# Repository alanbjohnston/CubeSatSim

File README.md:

# CubeSatSim

The CubeSat Simulator https://github.com/alanbjohnston/CubeSatSim/wiki is a low cost satellite emulator that runs on solar panels and batteries, transmits UHF radio telemetry, has a 3D printed frame, and can be extended by additional sensors and modules.  This project is sponsored by the not-for-profit [Radio Amateur Satellite Corporation, AMSAT®](https://amsat.org) https://CubeSatSim.org

The three custom PCBs are the Main, Battery and Solar boards.  Information including schematics and gerbers is in https://CubeSatSim.org/hardware

For information about the AMSAT STEM education program based on the CubeSatSim, see https://CubeSatSim.org/EducatorsGuide

For STEM activities to do with the CubeSatSim, see the https://CubeSatSim.org/ActivityGuides

There are several hardware versions and software branches to go with them - see below for information.

See the Wiki Software Install page for more details: https://github.com/alanbjohnston/CubeSatSim/wiki/2.-Software-Install. The software runs the Raspberry Pi Zero 2W and the Raspberry Pi 4B.  Some of the software runs on a Raspberry Pi 3B, 3B+, Pi Zero, and Pi Zero W.

There are two ways to get the CubeSatSim(TM) software for your Pi.

One option is to download the disk image file and write it to a 16GB micro SD card or larger.  The image is based on Raspberry Pi OS (Bookworm) Legacy. All software is installed, you just need to login to change your password and set your amateur radio callsign if you have one.  You can run the ./update.sh script to update all packages and update and compile the latest CubeSatSim software.

The other option is to start with a Raspberry Pi OS (Rasbian) image (Bookworm Legacy - Trixie is not yet compatible) and run the installation script ./install.sh which will install and compile all the related software.  This includes the following packages:
- wiringpi
- git
- libasound2-dev
- pi-power-button
- Direwolf
- rpitx
- python3-pip
- python3-smbus

## Disk Image Option Steps

See the Wiki Software Install page for details: [https://github.com/alanbjohnston/CubeSatSim/wiki/2.-Software-Install](https://github.com/alanbjohnston/CubeSatSim/wiki/2.-Software-Install#disk-image-option-steps).

## Installation Script Option Steps

Use the Raspberry Pi Imager https://www.raspberrypi.com/software/ and select the Bookworm Legacy option.  Make sure you set your username as pi.  You can also preset your password, localization, and WiFi settings.

       cd
       git clone http://github.com/alanbjohnston/CubeSatSim.git
       cd CubeSatSim
       git checkout master
       ./install

The installation script will run for quite a while.  You will get prompted for your amateur radio callsign in all capitals, if you have one.  If you don't you can put some other word which will be transmitted as a CW ID.  You will also be prompted for your latitude and longitude for APRS packets.  You will need to reboot after the script completes.

Here are some Quick Start Guides for operating the CubeSatSim: https://CubeSatSim.org/qsg

If you want to run the software on a Raspberry Pi Zero or Pi Zero W, you can install it on Bullseye.  Here is a Bullseye Pi OS image that works: https://downloads.raspberrypi.org/raspios_full_armhf/images/raspios_full_armhf-2023-05-03/ Here is the file download link: https://downloads.raspberrypi.org/raspios_full_armhf/images/raspios_full_armhf-2023-05-03/2023-05-03-raspios-bullseye-armhf-full.img.xz

You can use this with the Raspberry Pi Imager, but under `OS` you need to choose the `Use Custom` option at the very bottom of the list, then select the downloaded image `2023-05-03-raspios-bullseye-armhf-full.img.xz`

Unfortunately, Customization is not supported with a Custom image, so you can't preset your username, password, localization, and WiFi settings.

So after you write this image to your microSD card, you will need to connect a monitor and keyboard to your Pi Zero 2 to set these things (make sure you set `pi` as the username). After that, you can connect it to your WiFi and turn on ssh and vnc for remote access.

You can then follow the software installation steps and it work work.  The only hiccup is that if you run the installer script while running the Desktop, the Direwolf installation will freeze.  But you can just cycle the power to the Pi Zero 2, then run the installer script again and it will complete successfully.  Alternatively, if you use `sudo raspi-config` to change to Boot to Console (System/ Boot Auto Login/ Console or Console Auto Login) then the installer script will complete without any issues.

*Note:* CubeSatSim expects to be installed as the `pi` user and references many paths in `/home/pi/*`. Installing as a different user will result in configuration files not saving along with many other issues.

To install the software follow the steps above.

Older Versions

There are several versions of the hardware and software to go with them:

- The original design used a Digital Transceiver Board for the Raspberry Pi (DigitalTxRxRPi) and APRS AFSK 1200 bps telemetry only.  Use the aprs-digitaltxrx branch https://github.com/alanbjohnston/CubeSatSim/tree/aprs-digitaltxrx for this and the vB2 wiki page https://github.com/alanbjohnston/CubeSatSim/wiki/vB2-Home (e.g. run `git checkout aprs-digitaltxrx` before running the ./install.sh script)
- An updated design that used the Transmitter/Filter Board (TFB) instead of the the Transceiver Board.  For the same APRS AFSK telemetry, use the aprs-rpitx branch https://github.com/alanbjohnston/CubeSatSim/tree/aprs-rpitx and the vB3 wiki page https://github.com/alanbjohnston/CubeSatSim/wiki/vB3-Home. (e.g. run `git checkout aprs-rpitx` before running the ./install.sh script) Note that this hardware can still use the master code branch.

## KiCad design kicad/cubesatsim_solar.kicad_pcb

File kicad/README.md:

Schematic for vB3 Solar Panel Board in KiCad

For the latest PCB hardware see https://github.com/alanbjohnston/CubeSatSim/tree/master/hardware/

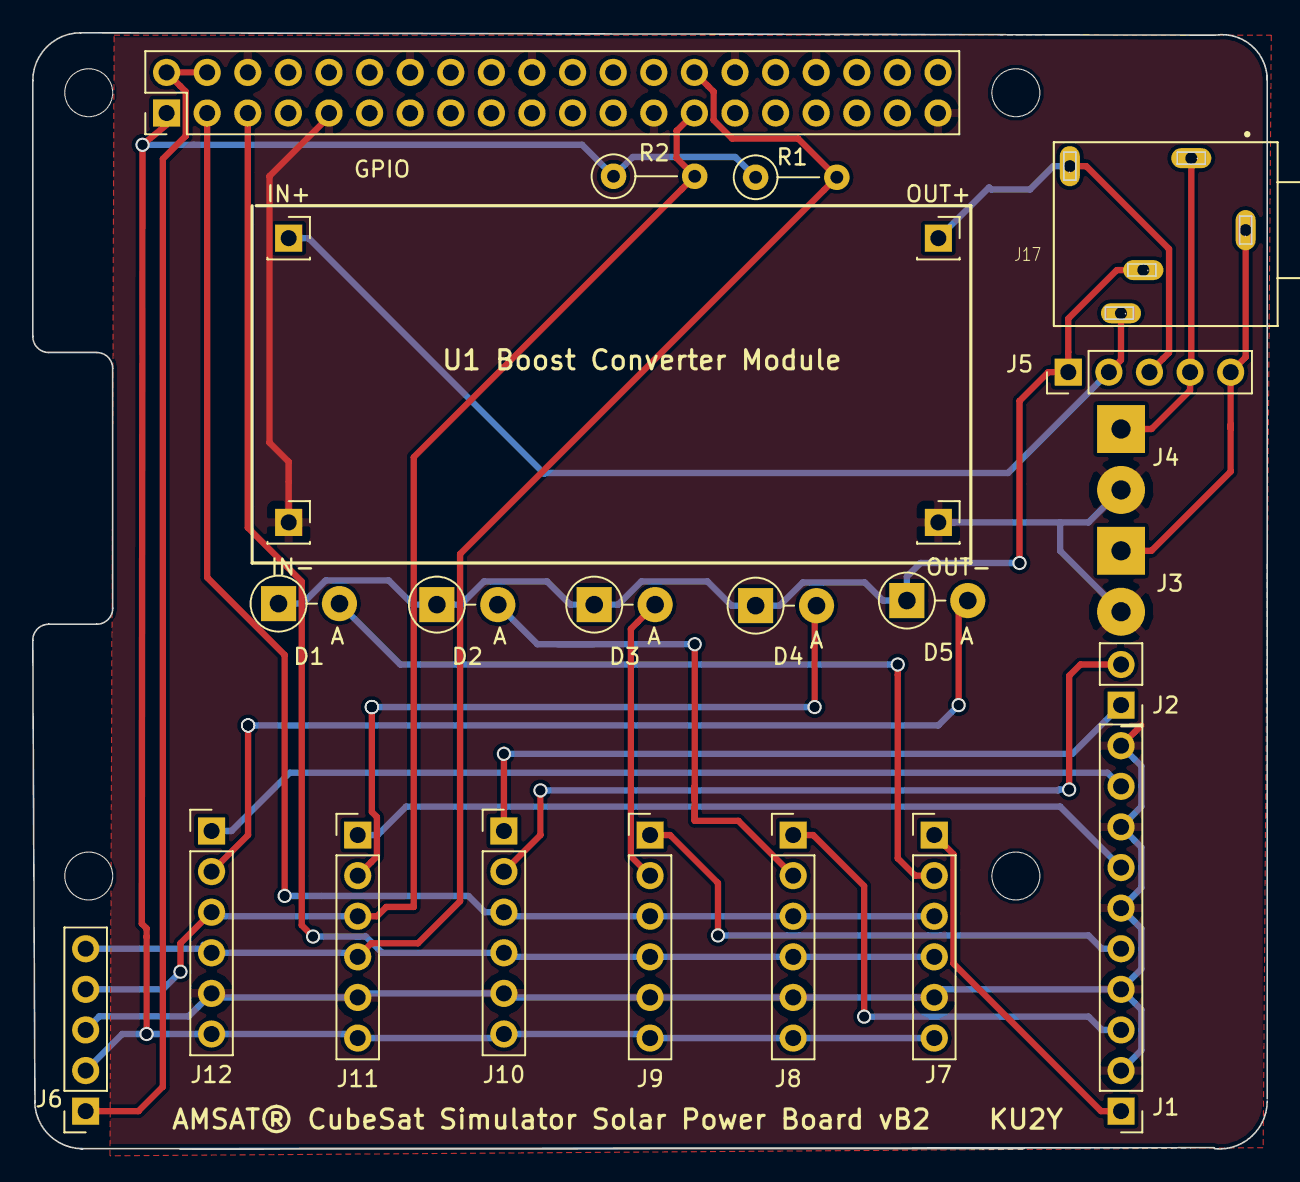
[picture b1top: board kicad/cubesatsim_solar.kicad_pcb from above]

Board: 2 copper layers, 77.2 x 69.8 mm, 25 parts (0 on the bottom side), 24 nets.

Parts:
D1, D2, D3, D4, D5: 1N5817; D_DO-41_SOD81_P3.81mm_Vertical_AnodeUp
GPIO: GPIO Male Extra Long (19mm) 20x2 Header Pins; PinHeader_2x20_P2.54mm_Vertical
IN+: IN+; PinSocket_1x01_P2.54mm_Vertical
IN-: IN-; PinSocket_1x01_P2.54mm_Vertical
J1: Sensor Inputs; PinHeader_1x10_P2.54mm_Vertical
J2: Battery In/Out; PinHeader_1x02_P2.54mm_Vertical
J3: Vdc In; SolderWirePad_1x02_P3.81mm_Drill1.2mm
J4: Vout to MoPOWER; SolderWirePad_1x02_P3.81mm_Drill1.2mm
J5: RBF Switch; PinHeader_1x05_P2.54mm_Vertical
J6: Expansion Interface; PinSocket_1x05_P2.54mm_Vertical
J7, J8, J9, J10, J11, J12: INA219 Sensor Board; PinHeader_1x06_P2.54mm_Vertical
J17: SWITCHCRAFT_35RAPC4BH3
OUT+: OUT+; PinSocket_1x01_P2.54mm_Vertical
OUT-: OUT-; PinSocket_1x01_P2.54mm_Vertical
R1, R2: 4.7k; R_Axial_DIN0207_L6.3mm_D2.5mm_P5.08mm_Vertical

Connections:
+3V3: GPIO.1, J6.2, J7.6, J8.6, J9.6, J10.6, J11.6, J12.6, R1.1, R2.1
+5V: GPIO.2, GPIO.4, J6.1
GND: GPIO.6, GPIO.9, GPIO.14, GPIO.20, GPIO.25, GPIO.30, GPIO.34, GPIO.39, IN-.1, J1.2, J1.4, J1.6, J1.8, J1.10, J3.2, J4.2, J6.3, J7.5, J8.5, J9.5, J10.5, J11.5, J12.5, OUT-.1
unnamed: D1.1, D2.1, D3.1, D4.1, D5.1, J5.1, J17.3
unnamed: IN+.1, J5.2, J17.2
unnamed: J5.3, J17.4, OUT+.1
unnamed: J3.1, J5.5, J17.1
unnamed: J4.1, J5.4, J17.5
SCL_1: GPIO.5, J7.4, J8.4, J9.4, J10.4
SCL_3: GPIO.28, J6.5, J11.4, J12.4, R1.2
SDA_1: GPIO.3, J7.3, J8.3, J9.3, J10.3
SDA_3: GPIO.27, J6.4, J11.3, J12.3, R2.2
VbattIn: J2.1, J10.1
VbattOut: J2.2, J10.2
X+In: J1.1, J7.1
X+Out: D1.2, J7.2
X-In: J1.7, J11.1
X-Out: D4.2, J11.2
Y+In: J1.3, J8.1
Y+Out: D2.2, J8.2
Y-In: J1.9, J12.1
Y-Out: D5.2, J12.2
Z+In: J1.5, J9.1
Z+Out: D3.2, J9.2

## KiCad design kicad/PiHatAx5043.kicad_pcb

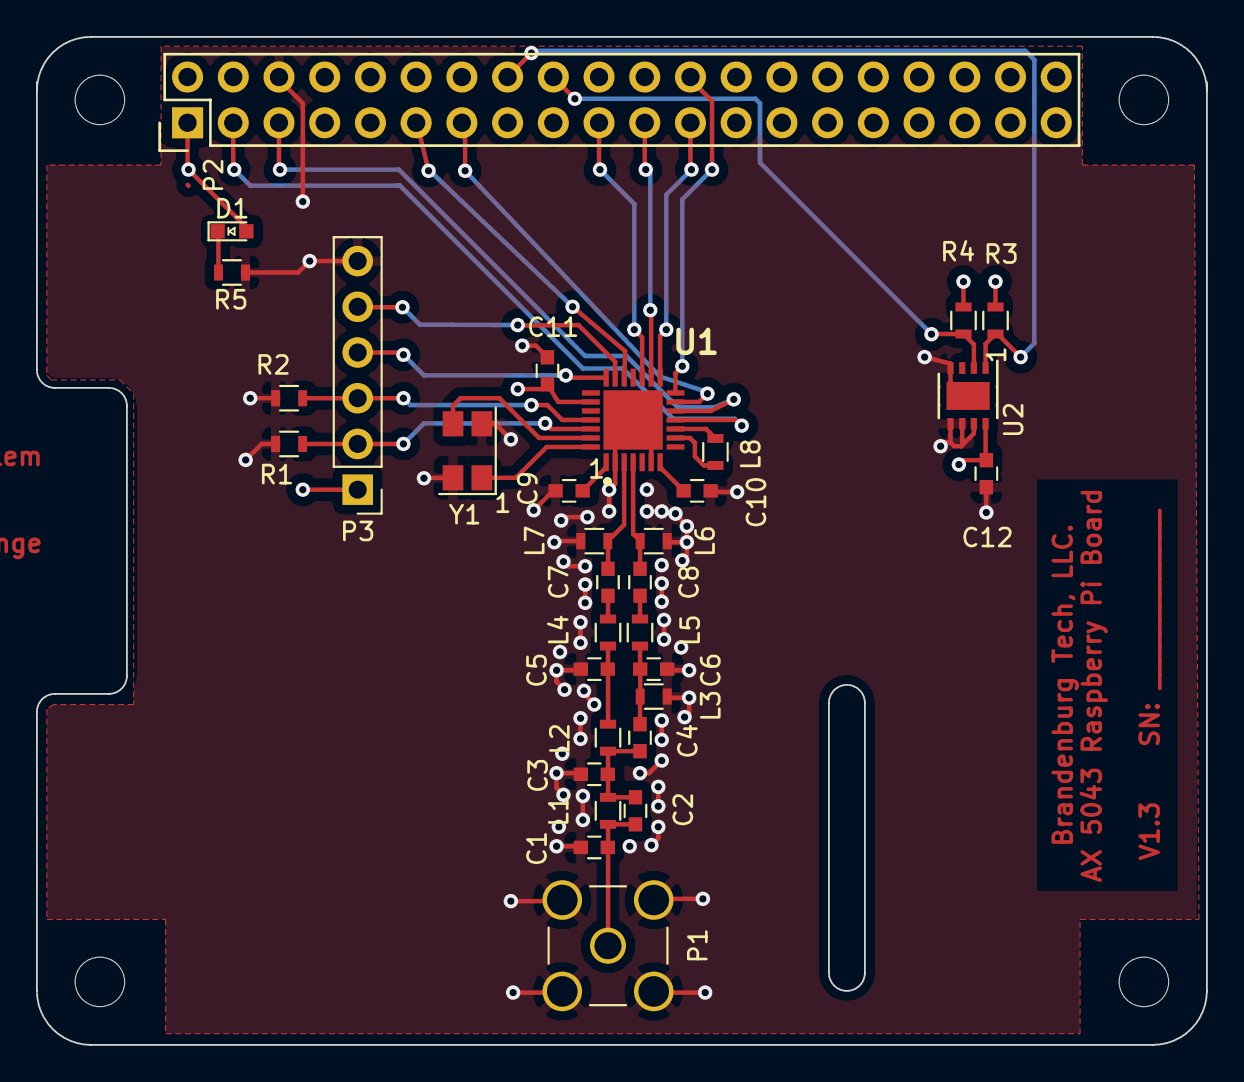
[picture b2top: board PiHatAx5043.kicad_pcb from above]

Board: 4 copper layers, 65.0 x 56.0 mm, 32 parts (0 on the bottom side), 31 nets.

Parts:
C1, C2, C3: NS; C_0603
C4: 5p1; C_0603
C5: 11p; C_0603
C6: 5p6; C_0603
C7, C8: 4p3; C_0603
C9, C10, C11: 10n; C_0603
C12: 100n; C_0603
D1: LED; LED_0603
L1, L8: 0R; L_0603
L2, L3: 27n; L_0603
L4, L5: 43n; L_0603
L6, L7: 100n; L_0603
P1: SMA; SMA_THT_Jack_Straight
P2: CONN_13X2; Pin_Header_Straight_2x20
P3: CONN_01X06; Pin_Header_Straight_1x06_Pitch2.54mm
R1, R2: 0R; R_0603
R3, R4: 4k7; R_0603
R5: R; R_0603
U1: AX5043; QFN50P500X500X95-29N
U2: MAX31725; DFN-8-1EP_3x3mm_Pitch0.65mm
Y1: 16M; Crystal_SMD_ECX42-4pin_4.0x2.5mm

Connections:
+3V3: C11.1, C12.1, D1.2, P2.1, P3.1, R3.1, R4.1, U1.23, U2.8
AX5043_CLK: P2.23, U1.15
AX5043_DATA: P2.3, U1.11
AX5043_DCLK: P2.5, U1.12
AX5043_GPADC1: P3.3, R2.1, U1.25
AX5043_GPADC2: P3.2, R1.1, U1.26
AX5043_IRQ: P2.11, U1.19
AX5043_MISO: P2.21, U1.16
AX5043_MOSI: P2.19, U1.17
AX5043_SEL: P2.24, U1.14
AX5043_SYSCLK: P2.13, U1.13
GND: C1.2, C3.2, C5.2, C6.2, C9.2, C10.2, C11.2, C12.2, L3.1, L6.1, L7.1, P1.2, P2.6, P3.6, R1.2, R2.2, R5.2, U1.2, U1.6, U1.29, U2.4, U2.5, U2.6, U2.7, U2.9, Y1.2, Y1.4
I2C_SCL: P2.18, R4.2, U2.2
I2C_SDA: P2.16, R3.2, U2.1
unnamed: C1.1, C2.2, L1.2, P1.1
unnamed: C2.1, C3.1, C4.2, L1.1, L2.2
unnamed: C4.1, C6.1, L3.2, L5.2
unnamed: C5.1, L2.1, L4.2
unnamed: C7.1, L7.2, U1.3
unnamed: C7.2, L4.1
unnamed: C8.1, L6.2, U1.4
unnamed: C8.2, L5.1
unnamed: C9.1, U1.1
unnamed: C10.1, U1.7
unnamed: D1.1, R5.1
unnamed: L8.1, U1.10
unnamed: L8.2, U1.9
unnamed: P3.4, U1.21
unnamed: P3.5, U1.20
unnamed: U1.27, Y1.3
unnamed: U1.28, Y1.1

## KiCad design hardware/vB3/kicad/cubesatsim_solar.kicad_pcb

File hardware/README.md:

The current CubeSatSim hardware is in the v2.0 folder https://github.com/alanbjohnston/CubeSatSim/tree/master/hardware/v2.0.  The folder contains gerbers, schematics, and images of the Main, Battery, and Solar boards.

For information on building the boards, see https://CubeSatSim.org/wiki.

Older beta versions of the hardware are in the other folders and should not be used.

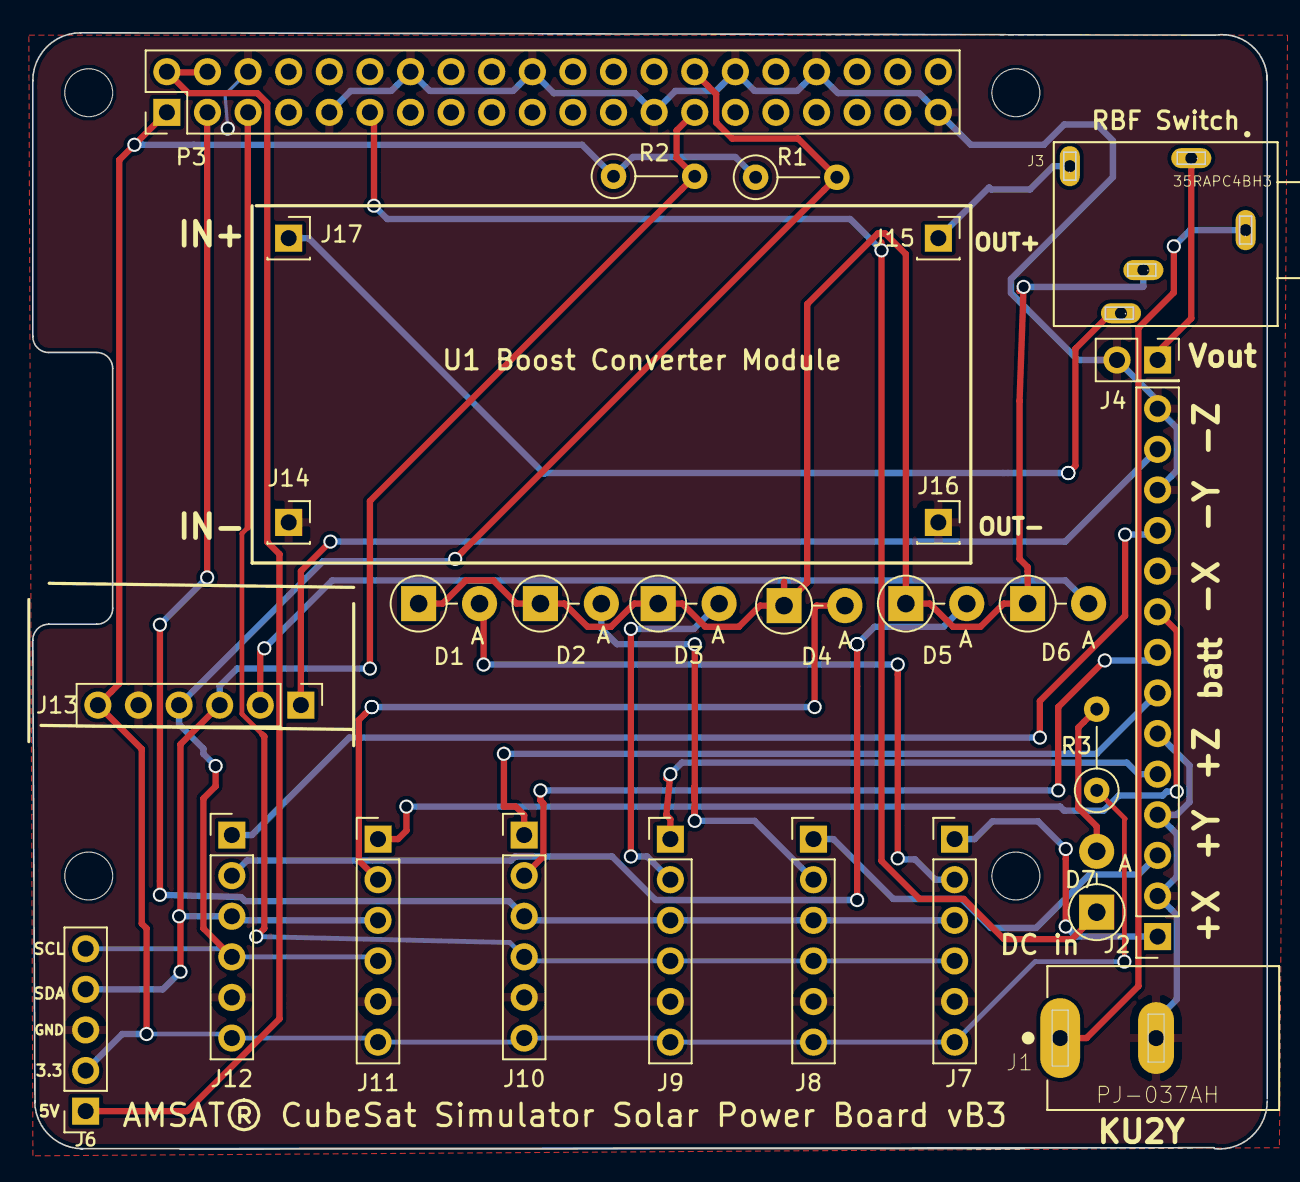
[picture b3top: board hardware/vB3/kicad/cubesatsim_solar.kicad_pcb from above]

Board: 2 copper layers, 77.2 x 69.8 mm, 27 parts (0 on the bottom side), 28 nets.

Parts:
D1, D2, D3, D4, D5, D6: 1N5817; D_DO-41_SOD81_P3.81mm_Vertical_AnodeUp
D7: LED; D_DO-41_SOD81_P3.81mm_Vertical_AnodeUp
J1: PJ-037AH; CUI_PJ-037AH
J2: CONN_01X14; PinSocket_1x14_P2.54mm_Vertical
J3: 35RAPC4BH3; SWITCHCRAFT_35RAPC4BH3
J4: Vout to MoPOWER; PinSocket_2x01_P2.54mm_Vertical
J6: Expansion Interface; PinSocket_1x05_P2.54mm_Vertical
J7, J8, J9, J10, J11, J12, J13: INA219 Sensor Board; PinHeader_1x06_P2.54mm_Vertical
J14: IN-; PinSocket_1x01_P2.54mm_Vertical
J15: OUT+; PinSocket_1x01_P2.54mm_Vertical
J16: OUT-; PinSocket_1x01_P2.54mm_Vertical
J17: IN+; PinSocket_1x01_P2.54mm_Vertical
P3: GPIO Male Extra Long (19mm) 20x2 Header Pins; PinHeader_2x20_P2.54mm_Vertical
R1, R2: 4.7k; R_Axial_DIN0207_L6.3mm_D2.5mm_P5.08mm_Vertical
R3: 220; R_Axial_DIN0207_L6.3mm_D2.5mm_P5.08mm_Vertical

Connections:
+3V3: J6.2, J7.6, J8.6, J9.6, J10.6, J11.6, J12.6, J13.6, P3.1, R1.1, R2.1, R3.1
+5V: J6.1, P3.2, P3.4
+X_In: J2.1, J7.1
+X_Out: D1.2, J7.2
+Y_In: J2.3, J8.1
+Y_Out: D2.2, J8.2
+Z_In: J2.5, J9.1
+Z_Out: D3.2, J9.2
-X_In: J2.9, J11.1
-X_Out: D4.2, J11.2
-Y_In: J2.11, J12.1
-Y_Out: D5.2, J12.2
-Z_In: J2.13, J13.1
-Z_Out: D6.2, J13.2
GND: J1.2, J2.2, J2.4, J2.6, J2.10, J2.12, J2.14, J4.2, J6.3, J7.5, J8.5, J9.5, J10.5, J11.5, J12.5, J13.5, J14.1, J16.1, P3.6, P3.9, P3.14, P3.20, P3.25, P3.30, P3.34, P3.39
unnamed: D1.1, D2.1, D3.1, D4.1, D5.1, D6.1, J3.3
unnamed: D7.1, P3.11
unnamed: D7.2, R3.2
unnamed: J1.1, J3.1
unnamed: J3.5, J4.1
unnamed: J3.4, J15.1
unnamed: J3.2, J17.1
SCL_1: J7.4, J8.4, J9.4, J10.4, P3.5
SCL_3: J6.5, J11.4, J12.4, J13.4, P3.28, R1.2
SDA_1: J7.3, J8.3, J9.3, J10.3, P3.3
SDA_3: J6.4, J11.3, J12.3, J13.3, P3.27, R2.2
VbattIn: J2.7, J10.1
VbattOut: J2.8, J10.2
